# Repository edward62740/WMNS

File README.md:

# Wireless Mesh Network System (WMNS)

## Overview

This is a wireless sensor network system as a part of an ongoing project for smart home sensing and security. The intent is to create easily deployable, low-maintenance (thereby low-power) sensors for real-time collection of non-sensitive data. The various sensors have a battery life typically between 1-4 years off a CR2032 (excl. CO2SN - 4 months, Li-ion).
The data is collected in InfluxDB and can be viewed graphically in Grafana.

## Related Development
_These devices either contribute to the WMNS database or utilize it for their functions._<br>
[PMS](https://github.com/edward62740/wmns-pms) - Particulate matter sensor.<br>
[IN-16 Display](https://github.com/edward62740/wmns-in16) - IN-16 tubes for displaying database information.<br>
[E-Paper Display](https://github.com/edward62740/wmns-epd) - Simple Wi-Fi/BLE enabled e-paper display. Designed for displaying real-time sensor data.<br>
[Lamp](https://github.com/edward62740/wmns-epd) - Mood lamp simulating candle flicker.<br>
[Transposer](https://github.com/edward62740/wmns-transposer) - Python script to transfer data from InfluxDB to Firebase RTDB.<br>

## Network Structure
This wireless mesh network is a proprietary, decentralized flood type network. The network consists of three distinct node types: routers (R), gateways (GT) and low-power end devices (LP).\
Routers retransmit received data to form the backbone of the network.\
Gateways are similar to routers and forward mesh network data to a server/cloud.\
End devices are low-power nodes that sleep for most of the time, periodically transmitting data.

## Measured data
Currently, the following data is collected by the system through multiple sensor types (sensors in brackets, not necessarily utilized as such):
* Temperature (BME280, BME680, Si7021, SCD41, BMA400, mcu_internal)
* Relative humidity (BME280, BME680, Si7021, SCD41)
* Barometric pressure (BME280, BME680)
* Illuminance (OPT3001, VEML6030, Si1133/5)
* UV levels (Si1133/5)
* Sudden/discontinous motion (BMA400)
* Person counter (VL53L1X)
* CO2 concentration (SCD41)
* VOC concentration (BME680)
* Battery levels (ADC)
* Signal strength (radio)

## Custom Hardware Devices
GPSN             |  LRSN      |  CO2SN  | ALSN
:-------------------------:|:-------------------------:|:-------------------------:|:-------------------------:
<br />General-purpose configurable sensor for: temperature, humidity, air pressure, light, VOCs, motion|<br />Person counter sensor |  <br />Carbon dioxide concentration sensor | <br />Specialized light sensor for visible, UV, IR

GATEWAY             |  ROUTER32PA      |  ROUTER40  | LTSN | TERMINAL
:-------------------------:|:-------------------------:|:-------------------------:|:-------------------------:|:-------------------------:
<br />Internet gateway node  |<br />Power amplified router node |  <br />USB-powered router node |<br />Specialized temp sensor for sub-zero|<br />Security node and gateway redundancy.

## Performance

The following performance factors were considered during the design of the WMNS:
* Low maintenance - essentially long battery life and reliability
</br> _Low power circuit and software design from bottom up. Certain sensors (i.e those expected to face harsher conditions) are conformally coated to increase reliability._
</br> _Network has no central "coordinator" type node which is required to sustain the network. Packets can take multiple paths to the gateway. Gateways can be configured as redundancies._
</br> _Connectionless protocol. No risk of runtime disconnections, failed acks etc. Sensors only need initial positioning in an area with good RSSI and reasonable packet loss from multipath fading._
* Ease of use - able to easily add more sensors (and more types), and modify configurations.
</br> _Easy plug-and-play to add more sensors. Only the gateway needs modifications to add new sensor types (for database side processing)._
</br> _Sensors can easily be configured for different sample rates._
* Range - good wireless range vs power consumption compromise
</br> _Tuned internal antennas allow for lower tx power (and less power consumption)._ 
</br>
* Low-cost - cheap sensors
</br> _Runs off comparatively low-cost and widely used nRF52 series SoCs. Same design template was used across sensors to drop development time and costs._
</br> _No protocol overhead or IP costs involved._

## Deployment

This system has been deployed in stages since Q1 21 with zero system failures (e.g gateway restarts, sensor malfunctions and drops out of network, hardware failure).
</br>

</br>
Deployed devices: 28

<br>
This repo is released under the GPL-2.0 License. Related repos DO NOT INHERIT licenses.

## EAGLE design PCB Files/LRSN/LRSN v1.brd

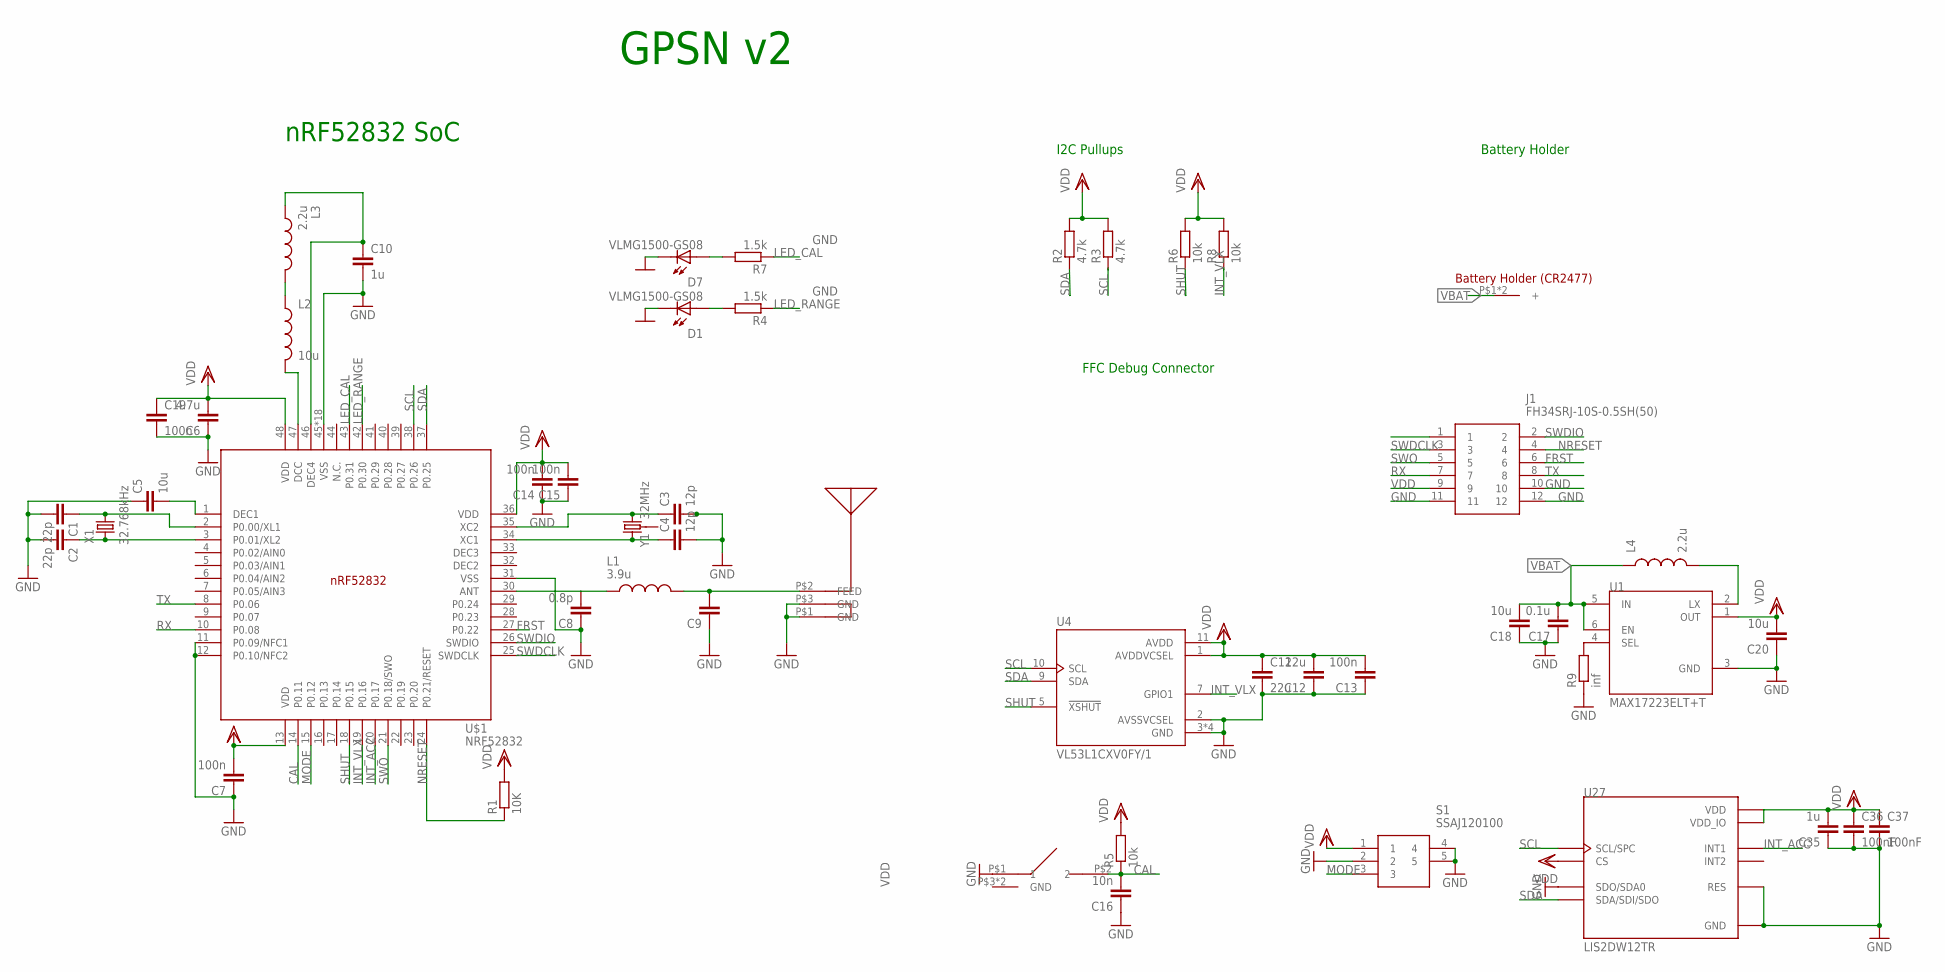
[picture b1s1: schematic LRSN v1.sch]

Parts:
C1, C2: 22p; C0402
C3, C4: 12p; C0402
C5, C18, C20: 10u; C0402
C6: 4.7u; C0402
C7: 100n; C0603R
C8: 0.8p; C0402
C9: 1.2p; C0402
C10: 1u; C0402
C11, C12: 22u; C0603R
C13, C14, C15, C19: 100n; C0402
C16: 10n; C0402
C17: 0.1u; C0402
C35: 1u; C0603R
C36, C37: 100nF; C0402
D1, D7: VLMG1500-GS08; LEDC1005X35N
J1: FH34SRJ-10S-0.5SH(50); FH34SRJ10S05SH50
L1: 3.9u; INDC0402X26N
L2: 10u; L0603
L3: 2.2u; INDC0402X26N
L4: 2.2u; L0603
R1: 10K; R0402
R2, R3: 4.7k; R0402
R4, R7: 1.5k; R0402
R5, R6, R8: 10k; R0402
R9: inf; R0402
S1: SSAJ120100
U1: MAX17223ELT+T; PSON65P200X200X80-6N
U4: VL53L1CXV0FY/1; SENSOR_VL53L1CXV0FY/1
U27: LIS2DW12TR; LGA12R50P4X4_200X200X70
U$1: NRF52832; QFN40P600X600X90-48_N
U$3: T1C2QR
U$4: CHIPANTENNAL2
VBAT: CR2477HOLDER
X1: 32.768kHz; ABS07-32.768KHZ-T
Y1: 32MHz; CRYSTAL-SMD-3.2X2.5MM

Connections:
CAL: C16.2, R5.1, U$1.14 (P0.11), U$3.P$2 (2)
FRST: J1.6, U$1.27 (P0.22)
GND: C1.2, C2.2, C3.2, C4.2, C5.1, C6.1, C7.1, C8.1, C9.1, C10.2, C11.2, C12.1, C13.1, C14.1, C15.1, C16.1, C17.1, C18.1, C19.2, C20.1, C35.1, C36.2, C37.2, D1.2, D7.2, J1.10, J1.11, J1.12, R9.1, S1.2, S1.4, S1.5, U1.3 (GND), U4.2 (AVSSVCSEL), U4.3 (GND), U4.4 (GND), U4.6 (GND), U4.12 (GND), U27.3 (SDO/SDA0), U27.6 (GND), U27.7 (RES), U27.8 (GND), U$1.11 (P0.09/NFC1), U$1.12 (P0.10/NFC2), U$1.31 (VSS), U$1.45 (VSS), U$1.PAD (VSS), U$1.PAD@VIA01 (VSS), U$1.PAD@VIA02 (VSS), U$1.PAD@VIA03 (VSS), U$1.PAD@VIA04 (VSS), U$1.PAD@VIA05 (VSS), U$1.PAD@VIA06 (VSS), U$1.PAD@VIA07 (VSS), U$1.PAD@VIA08 (VSS), U$1.PAD@VIA09 (VSS), U$1.PAD@VIA10 (VSS), U$1.PAD@VIA11 (VSS), U$1.PAD@VIA12 (VSS), U$1.PAD@VIA13 (VSS), U$1.PAD@VIA14 (VSS), U$1.PAD@VIA15 (VSS), U$1.PAD@VIA16 (VSS), U$3.P$1 (1), U$4.P$1 (GND), U$4.P$3 (GND)
INT_ACC: U27.12 (INT1), U$1.20 (P0.17)
INT_VLX: R8.1, U4.7 (GPIO1), U$1.19 (P0.16)
LED_CAL: R7.1, U$1.43 (P0.31)
LED_RANGE: R4.1, U$1.42 (P0.30)
MODE: S1.3, U$1.15 (P0.12)
unnamed: C1.1, U$1.2 (P0.00/XL1), X1.2
unnamed: C2.1, U$1.3 (P0.01/XL2), X1.1
unnamed: C3.1, U$1.35 (XC2), Y1.3 (2)
unnamed: C4.1, U$1.34 (XC1), Y1.1
unnamed: C5.2, U$1.1 (DEC1)
unnamed: C8.2, L1.1, U$1.30 (ANT)
unnamed: D1.1, R4.2
unnamed: R9.2, U1.4 (SEL)
unnamed: L2.2, U$1.47 (DCC)
unnamed: L2.1, L3.2
unnamed: C10.1, L3.1, U$1.46 (DEC4)
unnamed: L4.2, U1.2 (LX)
unnamed: D7.1, R7.2
NRESET: J1.4, R1.1, U$1.24 (P0.21/RESET)
RF: C9.2, L1.2, U$4.P$2 (FEED)
RX: J1.7, U$1.10 (P0.08)
SCL: R3.1, U4.10 (SCL), U27.1 (SCL/SPC), U$1.38 (P0.26)
SDA: R2.1, U4.9 (SDA), U27.4 (SDA/SDI/SDO), U$1.37 (P0.25)
SHUT: R6.1, U4.5 (!XSHUT), U$1.18 (P0.15)
SWDCLK: J1.3, U$1.25 (SWDCLK)
SWDIO: J1.2, U$1.26 (SWDIO)
SWO: J1.5, U$1.21 (P0.18/SWO)
TX: J1.8, U$1.8 (P0.06)
VBAT: C17.2, C18.2, L4.1, U1.5 (IN), U1.6 (EN), VBAT.P$1, VBAT.P$2
VDD: C6.2, C7.2, C11.1, C12.2, C13.2, C14.2, C15.2, C19.1, C20.2, C35.2, C36.1, C37.1, J1.9, R1.2, R2.2, R3.2, R5.2, R6.2, R8.2, S1.1, U1.1 (OUT), U4.1 (AVDDVCSEL), U4.11 (AVDD), U27.2 (CS), U27.9 (VDD), U27.10 (VDD_IO), U$1.13 (VDD), U$1.36 (VDD), U$1.48 (VDD)

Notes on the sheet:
nRF52832 SoC
I2C Pullups
Battery Holder
FFC Debug Connector
GPSN v2

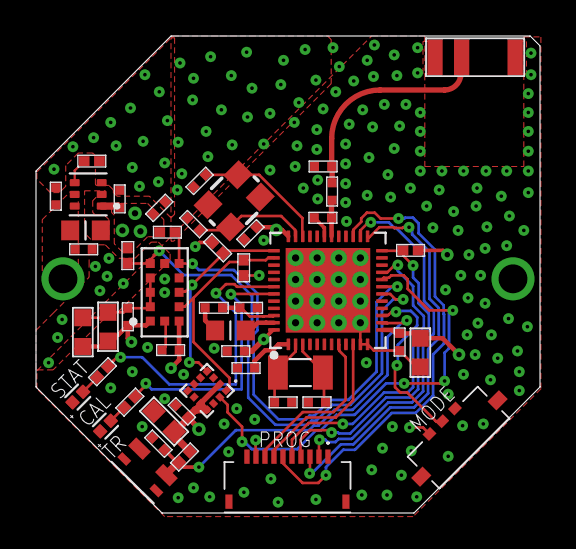
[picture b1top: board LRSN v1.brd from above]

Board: 4 copper layers, 28.0 x 26.5 mm, 49 parts (0 on the bottom side), 33 nets.

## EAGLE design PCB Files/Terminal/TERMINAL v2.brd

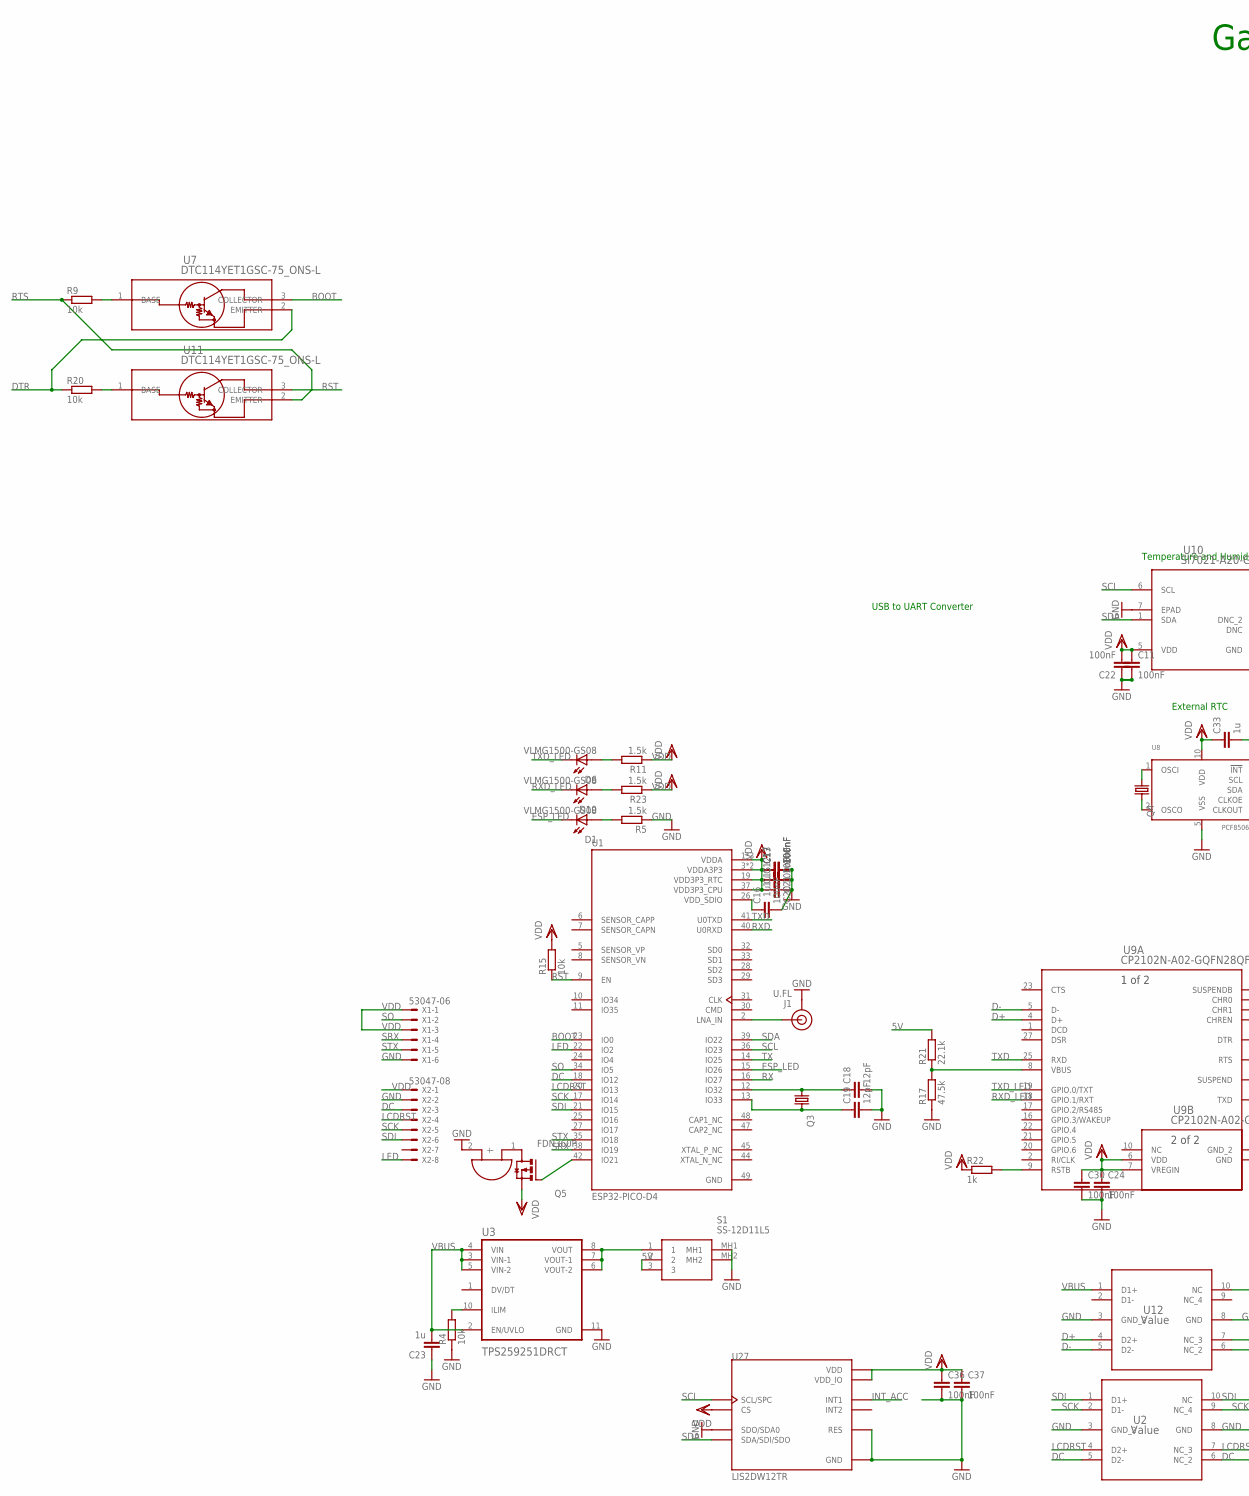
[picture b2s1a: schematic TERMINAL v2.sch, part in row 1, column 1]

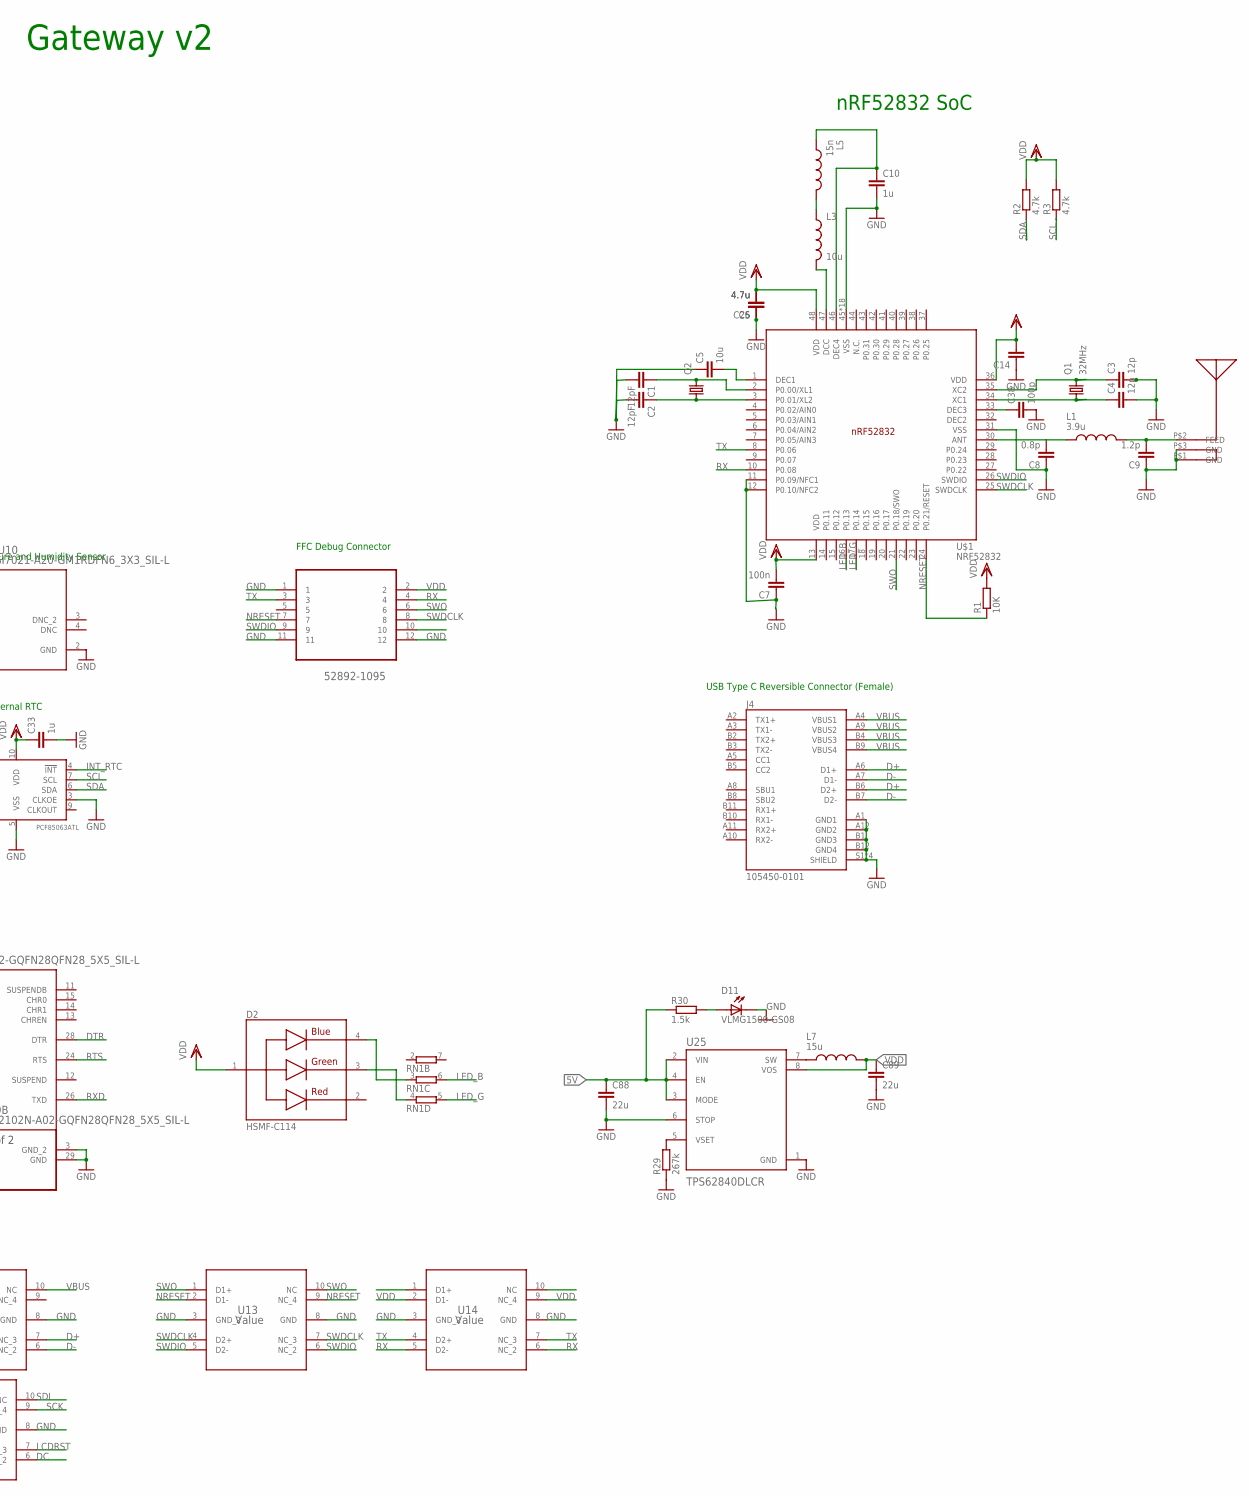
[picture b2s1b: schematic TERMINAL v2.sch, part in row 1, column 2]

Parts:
C1, C2, C18, C19: 12pF; C0402
C3, C4: 12p; C0402
C5: 10u; C0402
C6, C25: 4.7u; C0402
C7: 100n; C0402
C8: 0.8p; C0402
C9: 1.2p; C0402
C10: 1u; C0402
C11, C12, C13, C15, C16, C17, C22, C24, C30, C36, C37: 100nF; C0402
C14: 100u; C0402
C20, C21, C23, C33: 1u; C0603R
C38: 100p; C0402
C88, C89: 22u; C0603R
D1, D6, D10, D11: VLMG1500-GS08; LEDC1005X35N
D2: HSMF-C114; DIOSC160X150X35-4N
J1: U.FL
J4: 105450-0101; MOLEX_105450-0101
L1: 3.9u; INDC0402X26N
L3: 10u; L0603
L5: 15n; INDC0402X26N
L7: 15u; INDC3225X120N
Q1: 32MHz; 2.0X1.6_KX-5
Q2, Q3, Q4: KX-327-RT; 2.0X1.2
Q5: FDN360P; SUPER-SOT3
R1: 10K; R0402
R2, R3: 4.7k; R0402
R4, R9, R15, R20: 10k; R0402
R5, R11, R23, R30: 1.5k; R0402
R17: 47.5k; R0402
R21: 22.1k; R0402
R22: 1k; R0402
R29: 267k; R0402
RN1: 4R-N0402ARV341; 4X0402ARV341
S1: SS-12D11L5; SS12D11L5
U1: ESP32-PICO-D4; PQFN50P700X700X104-49N
U2, U12, U13, U14: Value; DQA0010A
U3: TPS259251DRCT; VREG_V62/16624-01YE
U5: 52892-1095; MOLEX_52892-1095
U7, U11: DTC114YET1GSC-75_ONS-L; SC-75_ONS-L
U8: PCF85063ATL; SOT1197-1
U9: CP2102N-A02-GQFN28QFN28_5X5_SIL-L; QFN28_5X5_SIL-L
U10: SI7021-A20-GM1RDFN6_3X3_SIL-L; DFN6_3X3_SIL-L
U25: TPS62840DLCR; SON50P200X150X100-8N
U27: LIS2DW12TR; LGA12R50P4X4_200X200X70
U$1: NRF52832; QFN40P600X600X90-48_N
U$2: SMD_BUZZER
U$4: CHIPANTENNAL2
X1: 53047-06
X2: 53047-08

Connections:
5V: C88.1, R21.2, R30.1, S1.2, S1.3, U25.2 (VIN), U25.3 (MODE), U25.4 (EN)
BOOT: U1.23 (IO0), U7.3 (COLLECTOR)
D+: J4.A6 (D1+), J4.B6 (D2+), U9.4 (D+), U12.4 (D2+), U12.7 (NC_3)
D-: J4.A7 (D1-), J4.B7 (D2-), U9.5 (D-), U12.5 (D2-), U12.6 (NC_2)
DC: U1.18 (IO12), U2.5 (D2-), U2.6 (NC_2), X2.3
DTR: R20.1, U7.2 (EMITTER), U9.28 (DTR)
ESP_LED: D1.2, U1.15 (IO26)
GND: C1.2, C2.2, C3.2, C4.2, C5.1, C6.1, C7.1, C8.1, C9.1, C10.2, C11.2, C12.2, C13.2, C14.1, C15.2, C16.2, C17.2, C18.2, C19.2, C20.1, C21.1, C22.1, C23.1, C24.2, C25.1, C30.2, C33.2, C36.2, C37.2, C38.2, C88.2, C89.2, D11.2, J1.1 (GND), J1.2 (GND), J4.A1 (GND1), J4.A12 (GND2), J4.B1 (GND3), J4.B12 (GND4), J4.S1 (SHIELD), J4.S2 (SHIELD), J4.S3 (SHIELD), J4.S4 (SHIELD), R4.1, R5.1, R17.1, R29.1, S1.MH1, S1.MH2, U1.49 (GND), U2.3 (GND_2), U2.8 (GND), U3.11 (GND), U5.1, U5.11, U5.12, U8.3 (CLKOE), U8.5 (VSS), U9.3 (GND_2), U9.29 (GND), U10.2 (GND), U10.7 (EPAD), U12.3 (GND_2), U12.8 (GND), U13.3 (GND_2), U13.8 (GND), U14.3 (GND_2), U14.8 (GND), U25.1 (GND), U25.6 (STOP), U27.3 (SDO/SDA0), U27.6 (GND), U27.7 (RES), U27.8 (GND), U$1.11 (P0.09/NFC1), U$1.12 (P0.10/NFC2), U$1.31 (VSS), U$1.45 (VSS), U$1.PAD (VSS), U$1.PAD@VIA01 (VSS), U$1.PAD@VIA02 (VSS), U$1.PAD@VIA03 (VSS), U$1.PAD@VIA04 (VSS), U$1.PAD@VIA05 (VSS), U$1.PAD@VIA06 (VSS), U$1.PAD@VIA07 (VSS), U$1.PAD@VIA08 (VSS), U$1.PAD@VIA09 (VSS), U$1.PAD@VIA10 (VSS), U$1.PAD@VIA11 (VSS), U$1.PAD@VIA12 (VSS), U$1.PAD@VIA13 (VSS), U$1.PAD@VIA14 (VSS), U$1.PAD@VIA15 (VSS), U$1.PAD@VIA16 (VSS), U$2.2 (-), U$4.P$1 (GND), U$4.P$3 (GND), X1.6, X2.2
INT_ACC: U27.12 (INT1)
INT_RTC: U8.4 (!INT!)
LCDRST: U1.20 (IO13), U2.4 (D2+), U2.7 (NC_3), X2.4
LED: U1.22 (IO2), X2.8
LED_B: RN1.6 (2), U$1.16 (P0.13)
LED_G: RN1.5 (2), U$1.17 (P0.14)
unnamed: C1.1, Q2.2, U$1.2 (P0.00/XL1)
unnamed: C2.1, Q2.1, U$1.3 (P0.01/XL2)
unnamed: C3.1, Q1.3 (2), U$1.35 (XC2)
unnamed: C4.1, Q1.1, U$1.34 (XC1)
unnamed: C5.2, U$1.1 (DEC1)
unnamed: C8.2, L1.1, U$1.30 (ANT)
unnamed: J1.FEED (SIGNAL), U1.2 (LNA_IN)
unnamed: C16.1, U1.26 (VDD_SDIO)
unnamed: L3.2, U$1.47 (DCC)
unnamed: L3.1, L5.2
unnamed: C10.1, L5.1, U$1.46 (DEC4)
unnamed: C19.1, Q3.2, U1.13 (IO33)
unnamed: C18.1, Q3.1, U1.12 (IO32)
unnamed: Q5.3 (D), U$2.1 (+)
unnamed: C38.1, U$1.33 (DEC3)
unnamed: Q5.1 (G), U1.42 (IO21)
unnamed: S1.1, U3.6 (VOUT-2), U3.7 (VOUT-1), U3.8 (VOUT)
unnamed: D1.1, R5.2
unnamed: R4.2, U3.10 (ILIM)
unnamed: D2.3, RN1.4 (1)
unnamed: R17.2, R21.1, U9.8 (VBUS)
unnamed: D2.4, RN1.3 (1)
unnamed: R20.2, U11.1 (BASE)
unnamed: R9.2, U7.1 (BASE)
unnamed: Q4.1, U8.1 (OSCI)
unnamed: Q4.2, U8.2 (OSCO)
unnamed: R22.2, U9.9 (RSTB)
unnamed: D6.1, R11.2
unnamed: D10.1, R23.2
unnamed: L7.1, U25.7 (SW)
unnamed: R29.2, U25.5 (VSET)
unnamed: D11.1, R30.2
NRESET: R1.1, U5.7, U13.2 (D1-), U13.9 (NC_4), U$1.24 (P0.21/RESET)
RFP1: C9.2, L1.2, U$4.P$2 (FEED)
RST: R15.1, U1.9 (EN), U11.3 (COLLECTOR)
RTS: R9.1, U9.24 (RTS), U11.2 (EMITTER)
RX: U1.16 (IO27), U5.4, U14.5 (D2-), U14.6 (NC_2), U$1.10 (P0.08)
RXD: U1.40 (U0RXD), U9.26 (TXD)
RXD_LED: D10.2, U9.18 (GPIO.1/RXT)
SCK: U1.17 (IO14), U2.2 (D1-), U2.9 (NC_4), X2.5
SCL: R3.1, U1.36 (IO23), U8.7 (SCL), U10.6 (SCL), U27.1 (SCL/SPC)
SDA: R2.1, U1.39 (IO22), U8.6 (SDA), U10.1 (SDA), U27.4 (SDA/SDI/SDO)
SDI: U1.21 (IO15), U2.1 (D1+), U2.10 (NC), X2.6
SO: U1.34 (IO5), X1.2
SRX: U1.38 (IO19), X1.4
STX: U1.35 (IO18), X1.5
SWDCLK: U5.8, U13.4 (D2+), U13.7 (NC_3), U$1.25 (SWDCLK)
SWDCLK1: U14.1 (D1+)
SWDIO: U5.9, U13.5 (D2-), U13.6 (NC_2), U$1.26 (SWDIO)
SWO: U5.6, U13.1 (D1+), U13.10 (NC), U$1.21 (P0.18/SWO)
TX: U1.14 (IO25), U5.3, U14.4 (D2+), U14.7 (NC_3), U$1.8 (P0.06)
TXD: U1.41 (U0TXD), U9.25 (RXD)
TXD_LED: D6.2, U9.19 (GPIO.0/TXT)
VBUS: C23.2, J4.A4 (VBUS1), J4.A9 (VBUS2), J4.B4 (VBUS3), J4.B9 (VBUS4), U3.2 (EN/UVLO), U3.3 (VIN-1), U3.4 (VIN), U3.5 (VIN-2), U12.1 (D1+), U12.10 (NC)
VDD: C6.2, C7.2, C11.1, C12.1, C13.1, C14.2, C15.1, C17.1, C20.2, C21.2, C22.2, C24.1, C25.2, C30.1, C33.1, C36.1, C37.1, C89.1, D2.1, L7.2, Q5.2 (S), R1.2, R2.2, R3.2, R11.1, R15.2, R22.1, R23.1, U1.1 (VDDA), U1.3 (VDDA3P3), U1.4 (VDDA3P3), U1.19 (VDD3P3_RTC), U1.37 (VDD3P3_CPU), U1.43 (VDDA), U1.46 (VDDA), U5.2, U8.10 (VDD), U9.6 (VDD), U9.7 (VREGIN), U10.5 (VDD), U14.2 (D1-), U14.9 (NC_4), U25.8 (VOS), U27.2 (CS), U27.9 (VDD), U27.10 (VDD_IO), U$1.13 (VDD), U$1.36 (VDD), U$1.48 (VDD), X1.1, X1.3, X2.1

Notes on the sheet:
USB to UART Converter
External RTC
Temperature and Humidity Sensor
FFC Debug Connector
USB Type C Reversible Connector (Female)
nRF52832 SoC
Gateway v2

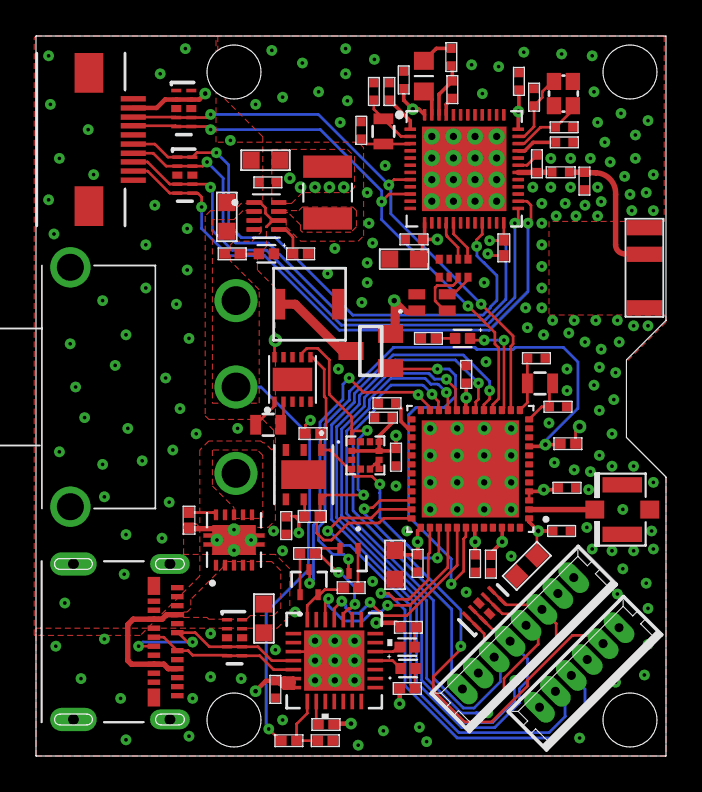
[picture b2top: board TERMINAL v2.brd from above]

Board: 4 copper layers, 35.0 x 40.0 mm, 84 parts (0 on the bottom side), 66 nets.

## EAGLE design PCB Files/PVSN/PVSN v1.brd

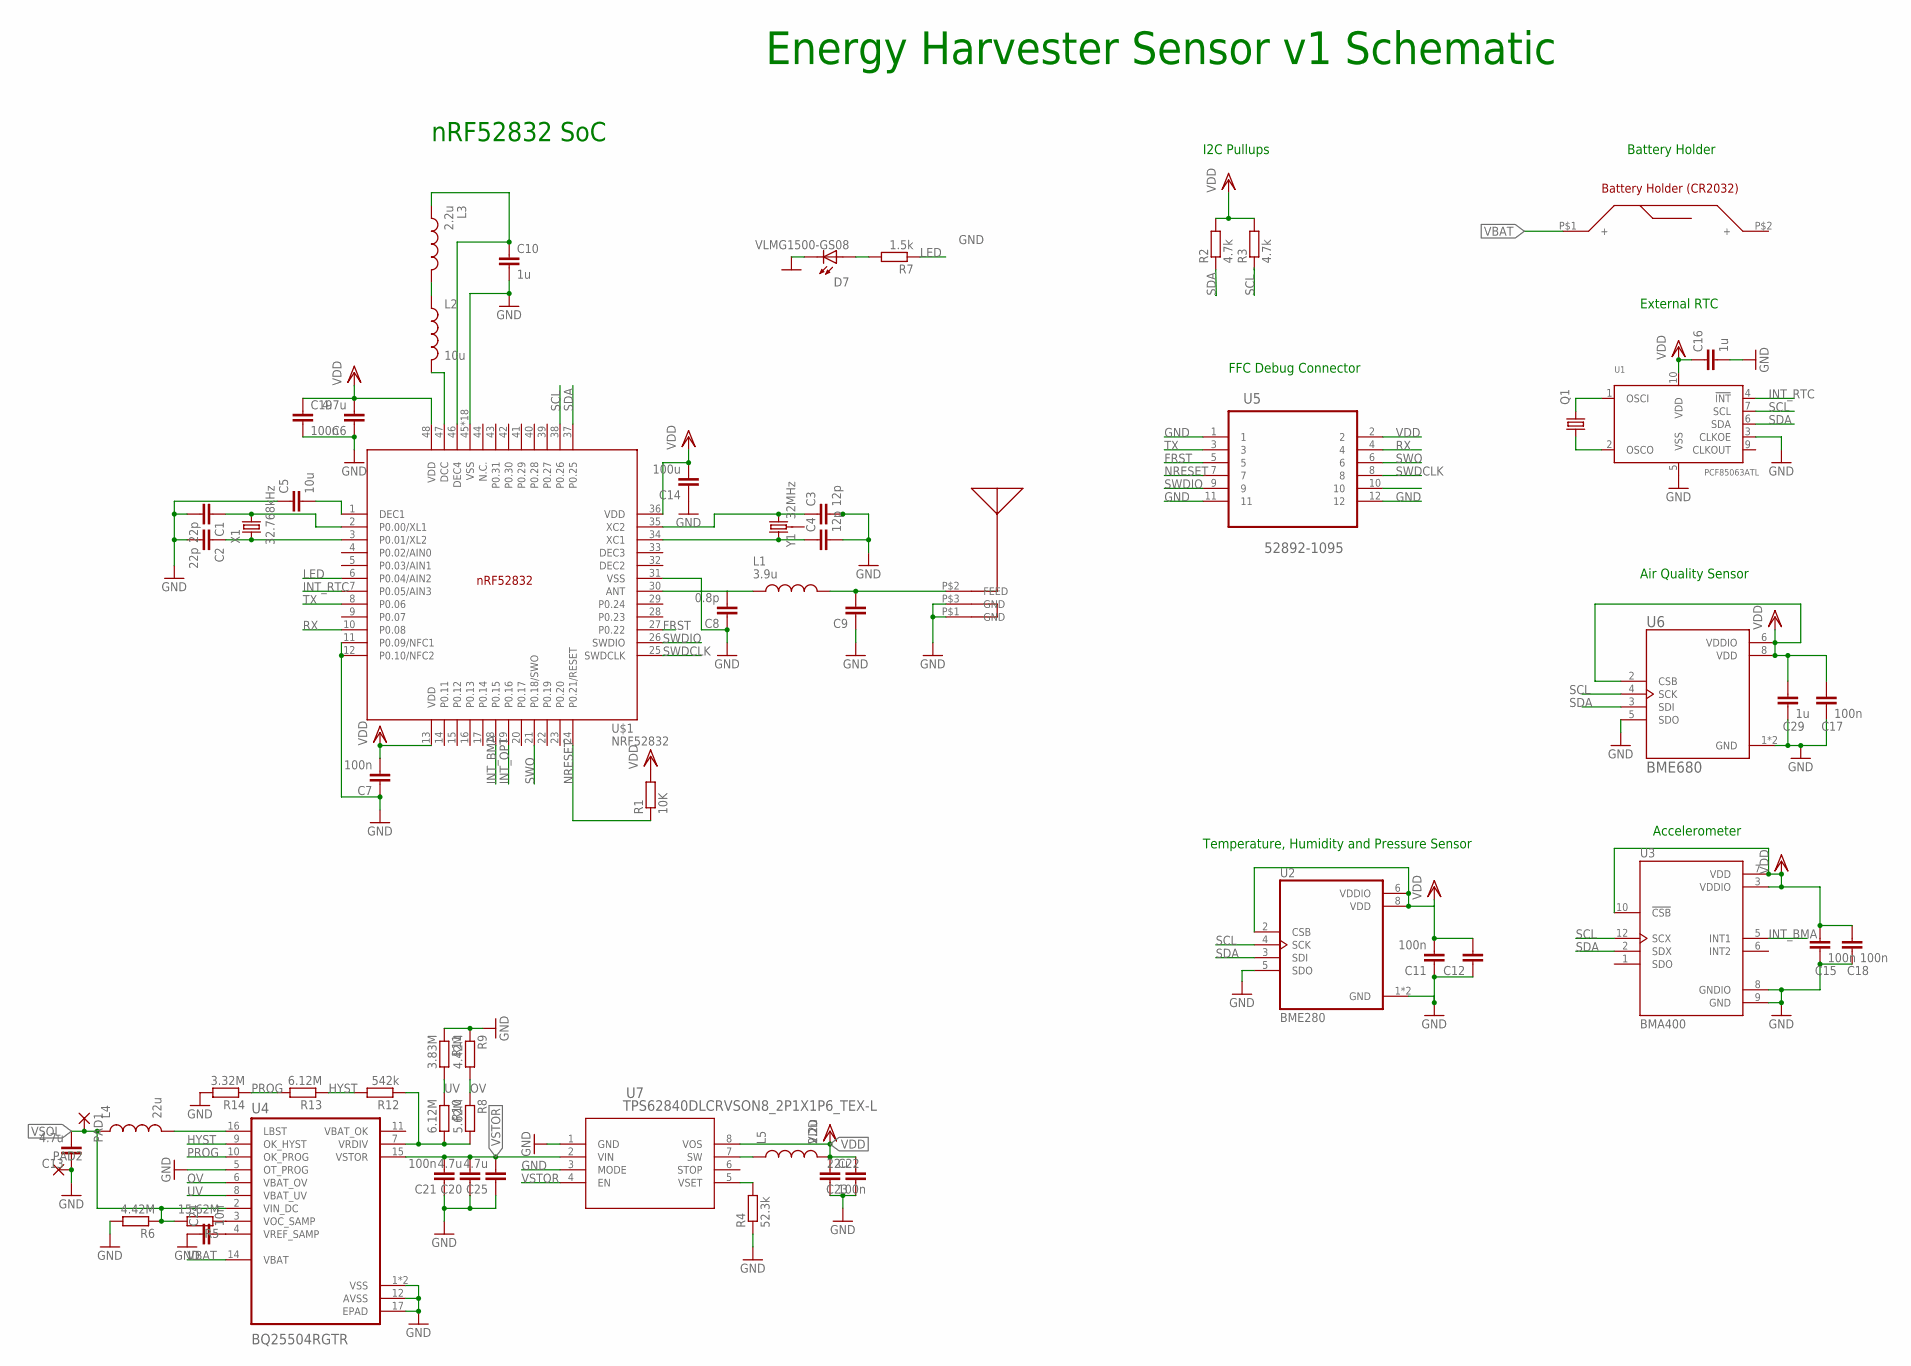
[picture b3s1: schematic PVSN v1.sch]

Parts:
C1, C2: 22p; C0402
C3, C4: 12p; C0402
C5: 10u; C0402
C6, C20, C25: 4.7u; C0402
C7: 100n; C0603R
C8: 0.8p; C0402
C9: 1.2p; C0402
C10, C12, C29: 1u; C0402
C11, C15, C17, C18, C19, C21, C22: 100n; C0402
C13: 4.7u; C0603R
C14: 100u; C0402
C16: 1u; C0603R
C23: 22u; C0603R
C24: 10n; C0402
D7: VLMG1500-GS08; LEDC1005X35N
L1: 3.9u; INDC0402X26N
L2: 10u; L0603
L3: 2.2u; INDC0402X26N
L4: 22u; L0603
L5: 2.2u; L0603
PAD1, PAD2: SMD2; SMD1,27-2,54
Q1: KX-327-RT; 2.0X1.2
R1: 10K; R0402
R2, R3: 4.7k; R0402
R4: 52.3k; R0402
R5: 15.62M; R0402
R6, R9: 4.42M; R0402
R7: 1.5k; R0402
R8: 5.62M; R0402
R10, R13: 6.12M; R0402
R11: 3.83M; R0402
R12: 542k; R0402
R14: 3.32M; R0402
U1: PCF85063ATL; SOT1197-1
U2: BME280; PSON65P250X250X100-8N
U3: BMA400; XDCR_BMA400
U4: BQ25504RGTR; QFN50P300X300X100-17N
U5: 52892-1095; MOLEX_52892-1095
U6: BME680; PSON80P300X300X100-8N
U7: TPS62840DLCRVSON8_2P1X1P6_TEX-L; VSON8_2P1X1P6_TEX-L
U$1: NRF52832; QFN40P600X600X90-48_N
U$2: HOLDER
U$4: CHIPANTENNAL2
X1: 32.768kHz; ABS07-32.768KHZ-T
Y1: 32MHz; CRYSTAL-SMD-3.2X2.5MM

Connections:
FRST: U5.5, U$1.27 (P0.22)
GND: C1.2, C2.2, C3.2, C4.2, C5.1, C6.1, C7.1, C8.1, C9.1, C10.2, C11.1, C12.1, C13.1, C14.1, C15.2, C16.2, C17.2, C18.2, C19.2, C20.1, C21.1, C22.2, C23.1, C24.1, C25.1, C29.2, D7.2, PAD2.1, R4.1, R6.2, R9.1, R11.1, R14.2, U1.3 (CLKOE), U1.5 (VSS), U2.1 (GND), U2.5 (SDO), U2.7 (GND), U3.8 (GNDIO), U3.9 (GND), U4.1 (VSS), U4.5 (OT_PROG), U4.12 (AVSS), U4.13 (VSS), U4.17 (EPAD), U5.1, U5.11, U5.12, U6.1 (GND), U6.5 (SDO), U6.7 (GND), U7.1 (GND), U7.3 (MODE), U$1.11 (P0.09/NFC1), U$1.12 (P0.10/NFC2), U$1.31 (VSS), U$1.45 (VSS), U$1.PAD (VSS), U$1.PAD@VIA01 (VSS), U$1.PAD@VIA02 (VSS), U$1.PAD@VIA03 (VSS), U$1.PAD@VIA04 (VSS), U$1.PAD@VIA05 (VSS), U$1.PAD@VIA06 (VSS), U$1.PAD@VIA07 (VSS), U$1.PAD@VIA08 (VSS), U$1.PAD@VIA09 (VSS), U$1.PAD@VIA10 (VSS), U$1.PAD@VIA11 (VSS), U$1.PAD@VIA12 (VSS), U$1.PAD@VIA13 (VSS), U$1.PAD@VIA14 (VSS), U$1.PAD@VIA15 (VSS), U$1.PAD@VIA16 (VSS), U$4.P$1 (GND), U$4.P$3 (GND)
HYST: R12.2, R13.1, U4.9 (OK_HYST)
INT_BMA: U3.5 (INT1), U$1.18 (P0.15)
INT_OPT: U$1.19 (P0.16)
INT_RTC: U1.4 (!INT!), U$1.7 (P0.05/AIN3)
LED: R7.1, U$1.6 (P0.04/AIN2)
unnamed: C1.1, U$1.2 (P0.00/XL1), X1.2
unnamed: C2.1, U$1.3 (P0.01/XL2), X1.1
unnamed: C3.1, U$1.35 (XC2), Y1.3 (2)
unnamed: C4.1, U$1.34 (XC1), Y1.1
unnamed: C5.2, U$1.1 (DEC1)
unnamed: C8.2, L1.1, U$1.30 (ANT)
unnamed: Q1.2, U1.1 (OSCI)
unnamed: Q1.1, U1.2 (OSCO)
unnamed: L2.2, U$1.47 (DCC)
unnamed: L2.1, L3.2
unnamed: C10.1, L3.1, U$1.46 (DEC4)
unnamed: L4.2, U4.16 (LBST)
unnamed: R8.2, R10.2, R12.1, U4.7 (VRDIV)
unnamed: L5.1, U7.7 (SW)
unnamed: R4.2, U7.5 (VSET)
unnamed: C24.2, U4.4 (VREF_SAMP)
unnamed: D7.1, R7.2
unnamed: R5.1, U4.3 (VOC_SAMP)
NRESET: R1.1, U5.7, U$1.24 (P0.21/RESET)
OV: R8.1, R9.2, U4.6 (VBAT_OV)
PROG: R13.2, R14.1, U4.10 (OK_PROG)
RF: C9.2, L1.2, U$4.P$2 (FEED)
RX: U5.4, U$1.10 (P0.08)
SCL: R3.1, U1.7 (SCL), U2.4 (SCK), U3.12 (SCX), U6.4 (SCK), U$1.38 (P0.26)
SDA: R2.1, U1.6 (SDA), U2.3 (SDI), U3.2 (SDX), U6.3 (SDI), U$1.37 (P0.25)
SWDCLK: U5.8, U$1.25 (SWDCLK)
SWDIO: U5.9, U$1.26 (SWDIO)
SWO: U5.6, U$1.21 (P0.18/SWO)
TX: U5.3, U$1.8 (P0.06)
UV: R10.1, R11.2, U4.8 (VBAT_UV)
VBAT: U4.14 (VBAT), U$2.P$1
VDD: C6.2, C7.2, C11.2, C12.2, C14.2, C15.1, C16.1, C17.1, C18.1, C19.1, C22.1, C23.2, C29.1, L5.2, R1.2, R2.2, R3.2, U1.10 (VDD), U2.2 (CSB), U2.6 (VDDIO), U2.8 (VDD), U3.3 (VDDIO), U3.7 (VDD), U3.10 (!CSB), U5.2, U6.2 (CSB), U6.6 (VDDIO), U6.8 (VDD), U7.8 (VOS), U$1.13 (VDD), U$1.36 (VDD), U$1.48 (VDD)
VSOL: C13.2, L4.1, PAD1.1, R5.2, R6.1, U4.2 (VIN_DC)
VSTOR: C20.2, C21.2, C25.2, U4.15 (VSTOR), U7.2 (VIN), U7.4 (EN)

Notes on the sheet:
nRF52832 SoC
I2C Pullups
Battery Holder
FFC Debug Connector
External RTC
Air Quality Sensor
Temperature, Humidity and Pressure Sensor
Accelerometer
Energy Harvester Sensor v1 Schematic

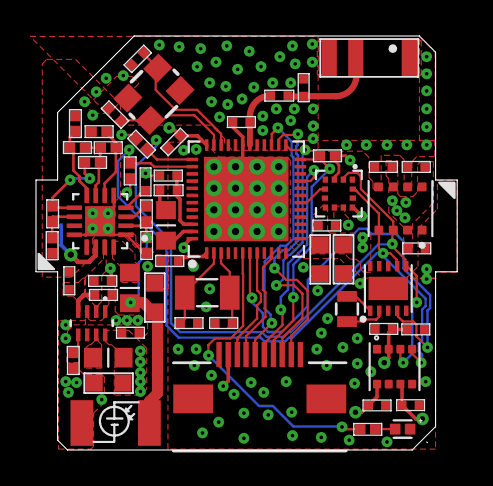
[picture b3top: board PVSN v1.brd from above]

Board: 4 copper layers, 23.4 x 23.0 mm, 61 parts (1 on the bottom side), 40 nets.

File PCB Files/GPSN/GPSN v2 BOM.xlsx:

Comment | Designator | Footprint
22p | C1 | C0402
22p | C2 | C0402
12p | C3 | C0402
12p | C4 | C0402
10u | C5 | C0402
4.7u | C6 | C0402
100n | C7 | C0603R
0.8p | C8 | C0402
1.2p | C9 | C0402
1u | C10 | C0402
100n | C11 | C0402
1u | C12 | C0402
100n | C13 | C0402
100u | C14 | C0402
100n | C15 | C0402
1u | C16 | C0603R
100n | C17 | C0402
100n | C18 | C0402
100n | C19 | C0402
1u | C29 | C0402
VLMG1500-GS08 | D7 | LEDC1005X35N
3.9u | L1 | INDC0402X26N
10u | L2 | L0603
2.2u | L3 | INDC0402X26N
2.0X1.2 | Q1
10K | R1 | R0402
4.7k | R2 | R0402
4.7k | R3 | R0402
1.5k | R7 | R0402
NRF52832 | U$1 | QFN40P600X600X90-48_N
TI-OPT3001 | U$3 | TI-OPT3001
CHIPANTENNAL2 | U$4 | CHIPANTENNAL2
PCF85063ATL | U1 | SOT1197-1
BME280 | U2 | PSON65P250X250X100-8N
BMA400 | U3 | XDCR_BMA400
52892-1095 | U5 | MOLEX_52892-1095
BME680 | U6 | PSON80P300X300X100-8N
32.768kHz | X1 | ABS07-32.768KHZ-T
32MHz | Y1 | CRYSTAL-SMD-3.2X2.5MM

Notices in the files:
parts and their libraries:
SparkFun-Clocks: Licensing: Creative Commons ShareAlike 4.0 International - https://creativecommons.org/licenses/by-sa/4.0
COPYRIGHT: Copyright (C) 2018 Accelerated Designs. All rights reserved
crystal-geyer_V1_0: Copyright: Geyer-Electronic
